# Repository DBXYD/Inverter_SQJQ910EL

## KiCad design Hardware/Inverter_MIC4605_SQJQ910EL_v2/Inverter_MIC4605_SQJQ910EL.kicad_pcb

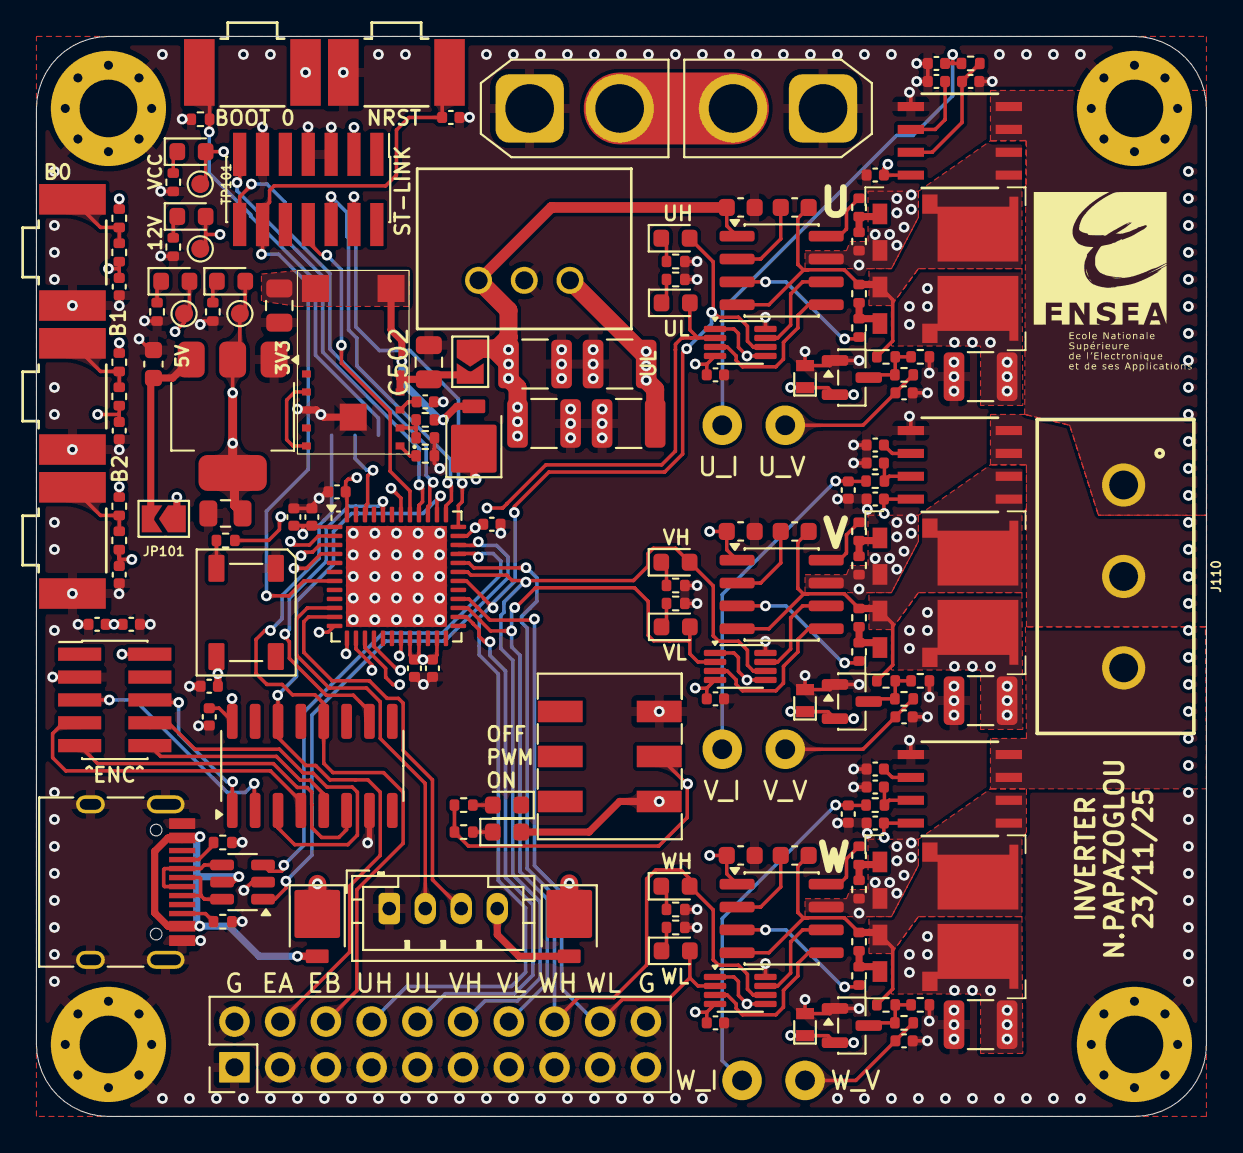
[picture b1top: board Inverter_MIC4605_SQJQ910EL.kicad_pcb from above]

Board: 6 copper layers, 65.0 x 60.0 mm, 170 parts (1 on the bottom side), 108 nets.

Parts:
C101, C102, C103, C104, C105, C119, C139, C140, C142, C207, C209, C307, C309, C407, C409: 100n; C_0402_1005Metric
C106: 4u7; C_0402_1005Metric
C107, C110, C128, C204, C205, C206, C208, C304, C305, C306, C308, C404, C405, C406, C408: 10n; C_0402_1005Metric
C108: 10u; C_0603_1608Metric
C109: 22u; C_0805_2012Metric
C141, C504: 1u; C_0402_1005Metric
C201, C202, C301, C302, C401, C402: 1u; C_0603_1608Metric
C203, C303, C403, C701, C702: 10u; C_1210_3225Metric
C502: 10u; C_0805_2012Metric
C503: 47u; C_0805_2012Metric
C703, C704: 22u; C_1210_3225Metric
D101, D103, D104: SS2P5-M3/84A; D_SMP_DO-220AA
D102: WS2812B; LED_WS2812B_PLCC4_5.0x5.0mm_P3.2mm
D105, D106, D107, D108, D109, D110, D201, D202, D301, D302, D401, D402: LED; LED_0603_1608Metric
D203, D303, D403: 824032813; WE 824032813
D204, D304, D404: BAT54S; SOT-23
H101, H102, H105, H106: MountingHole_Pad; MountingHole_3.2mm_M3_Pad_Via
J101, J102: Conn_01x02; AMASS_XT30U-M_1x02_P5.0mm_Vertical
J104: PinHeader_2x07_P1.27mm_Vertical_SMD
J106: 629722000214; USB_C_Receptacle_HRO_TYPE-C-31-M-12
J107: Conn_02x05_Odd_Even; PinHeader_2x05_P1.27mm_Vertical_SMD
J108: Conn_01x04; JST_PH_B4B-PH-K_1x04_P2.00mm_Vertical
J109: Conn_02x10_Odd_Even; PinHeader_2x10_P2.54mm_Vertical
J110: Conn_01x03; WE 691311500103
JP101, JP501: SolderJumper_2_Open; SolderJumper-2_P1.3mm_Open_TrianglePad1.0x1.5mm
JP102: Jumper_3_Open; SolderJumper-3_P1.3mm_Open_RoundedPad1.0x1.5mm
R101, R102, R103, R104, R106, R107, R112, R202, R205, R209, R210, R302, R305, R309, R310, R402, R405, R409, R410: 10k; R_0402_1005Metric
R105: 330; R_0402_1005Metric
R108: 12k; R_0402_1005Metric
R109: 10k2; R_0402_1005Metric
R110: 3k2; R_0402_1005Metric
R111, R206, R207, R306, R307, R406, R407: 1k5; R_0402_1005Metric
R113, R114: 1k1; R_0402_1005Metric
R115, R116: 5k1; R_0402_1005Metric
R201, R204, R301, R304, R401, R404: 33; R_0402_1005Metric
R203, R303, R403: 1k; R_0402_1005Metric
R208, R308, R408: 180k; R_0402_1005Metric
R501: 402k; R_0402_1005Metric
R502: 80k6; R_0402_1005Metric
R503: 5k6; R_0402_1005Metric
SW101, SW102, SW103, SW104, SW105: SW_Push; KSS221GLFS
SW106: SW_Slide_DPDT; WE 452406020024
TP101, TP102: 24V; TestPoint_Pad_D1.0mm
TP103: 5V; TestPoint_Pad_D1.0mm
TP104: 3V3; TestPoint_Pad_D1.0mm
TP105, TP106, TP107, TP108, TP109, TP110: Pin_D1.1mm_L8.5mm_W2.5mm_FlatFork
U101: AZ1117-3.3; SOT-223
U102: STM32G431CBUx; QFN-48-1EP_7x7mm_P0.5mm_EP5.6x5.6mm
U103: USBLC6-2SC6; SOT-23-6
U104: MAX3097ECSE+; SOIC-16_3.9x9.9mm_P1.27mm
U201, U301, U401: SQJQ910EL
U202, U302, U402: SN74LVC2G08; VSSOP-8_2.3x2mm_P0.5mm
U203, U303, U403: MIC4605-1YM; SOIC-8_3.9x4.9mm_P1.27mm
U204, U304, U404: GO 10-SME/SP3; SOIC8-GO-SME&slash_SP3_LEM
U501: WE 171013801
U701: WE 173951275

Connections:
+3.3V: C101.1, C102.1, C103.2, C104.1, C105.1, C106.1, C109.1, C140.2, C204.1, C207.1, C304.1, C307.1, C404.1, C407.1, D108.2 (A), D109.2 (A), D203.1 (A1), D204.2 (K), D303.1 (A1), D304.2 (K), D403.1 (A1), D404.2 (K), J104.3 (VCC), R101.2, R103.2, R106.2, SW104.1, SW106.1 (A), TP104.1, U101.2 (VO), U101.4 (VO), U102.1 (VBAT), U102.20 (VREF+), U102.21 (VDDA), U102.23 (VDD), U102.35 (VDD), U102.48 (VDD), U104.16 (VCC), U202.4 (GND), U204.8 (UC), U302.4 (GND), U304.8 (UC), U402.4 (GND), U404.8 (UC)
+5V: C119.2, C141.1, C142.2, D101.1 (K), D102.1 (VDD), D103.1 (K), D104.1 (K), D107.2 (A), J107.2, JP101.1 (A), TP103.1
+12V: C201.1, C301.1, C401.1, C703.1, C704.1, D106.2 (A), JP501.1 (A), TP102.1, U203.1 (Vdd), U303.1 (Vdd), U403.1 (Vdd), U701.3 (12V)
/5V_BUCK: C503.1, D101.2 (A), R501.1, U501.6 (VOUT), U501.7 (VOUT)
/5V_UART: D104.2 (A), J108.4
/5V_USB: D103.2 (A), J106.A4 (VBUS), J106.A9 (VBUS), J106.B4 (VBUS), J106.B9 (VBUS), U103.5 (VBUS)
/A: J107.6, U104.1 (A)
/B: J107.8, U104.3 (B)
/BOOT_0: JP102.1 (A), R112.2, SW104.2
/BTN_0: C107.1, R102.1, U102.2 (PC13)
/BTN_1: C110.1, R104.1, U102.3 (PC14)
/BTN_2: C128.1, R107.1, U102.4 (PC15)
/D+: J106.A6 (D+), J106.B6 (D+), U103.6 (I/O1)
/D-: J106.A7 (D-), J106.B7 (D-), U103.4 (I/O2)
/EXT_RX: J108.3, U102.11 (PA3)
/EXT_TX: J108.2, U102.10 (PA2)
/MIC4605_SQJQ910EL_U/BM: C202.2, R202.2, R208.2, U201.3 (S), U201.5 (D), U203.4 (HS), U204.1 (IP+), U204.2 (IP+)
/MIC4605_SQJQ910EL_U/CMD_H: R201.1, U203.3 (HO)
/MIC4605_SQJQ910EL_U/CMD_L: R204.1, U203.8 (LO)
/MIC4605_SQJQ910EL_U/HB: C202.1, U203.2 (HB)
/MIC4605_SQJQ910EL_U/Imes: C205.1, R203.1, U204.7 (UOUT)
/MIC4605_SQJQ910EL_U/Uref: C206.1, U204.6 (UREF)
/MIC4605_SQJQ910EL_V/BM: C302.2, R302.2, R308.2, U301.3 (S), U301.5 (D), U303.4 (HS), U304.1 (IP+), U304.2 (IP+)
/MIC4605_SQJQ910EL_V/CMD_H: R301.1, U303.3 (HO)
/MIC4605_SQJQ910EL_V/CMD_L: R304.1, U303.8 (LO)
/MIC4605_SQJQ910EL_V/HB: C302.1, U303.2 (HB)
/MIC4605_SQJQ910EL_V/Imes: C305.1, R303.1, U304.7 (UOUT)
/MIC4605_SQJQ910EL_V/Uref: C306.1, U304.6 (UREF)
/MIC4605_SQJQ910EL_W/BM: C402.2, R402.2, R408.2, U401.3 (S), U401.5 (D), U403.4 (HS), U404.1 (IP+), U404.2 (IP+)
/MIC4605_SQJQ910EL_W/CMD_H: R401.1, U403.3 (HO)
/MIC4605_SQJQ910EL_W/CMD_L: R404.1, U403.8 (LO)
/MIC4605_SQJQ910EL_W/HB: C402.1, U403.2 (HB)
/MIC4605_SQJQ910EL_W/Imes: C405.1, R403.1, U404.7 (UOUT)
/MIC4605_SQJQ910EL_W/Uref: C406.1, U404.6 (UREF)
/NEO_PWM: R105.1, U102.42 (PB4)
/NRST: C139.1, J104.12 (~RST), SW105.1, U102.7 (PG10)
/OUT_A: J109.4, U102.38 (PA15), U104.14 (OutA)
/OUT_B: J109.6, JP102.3 (B), U104.12 (OutB)
/OUT_Z: U102.44 (PB6), U104.10 (OutZ)
/PWM_EN: R113.2, R114.1, SW106.2 (B), U202.1, U202.5, U302.1, U302.5, U402.1, U402.5
/PWM_U_H: D201.2 (A), J109.8, U102.30 (PA8), U202.6
/PWM_U_L: D202.2 (A), J109.10, U102.26 (PB13), U202.2
/PWM_V_H: D301.2 (A), J109.12, U102.31 (PA9), U302.6
/PWM_V_L: D302.2 (A), J109.14, U102.27 (PB14), U302.2
/PWM_W_H: D401.2 (A), J109.16, U102.32 (PA10), U402.6
/PWM_W_L: D402.2 (A), J109.18, U102.28 (PB15), U402.2
/SWCLK: J104.6 (JCLK/SWCLK), U102.37 (PA14)
/SWDIO: J104.4 (JTMS/SWDIO), U102.36 (PA13)
/SWO: J104.8 (JTDO/SWO), U102.41 (PB3)
/USB_DN: U102.33 (PA11), U103.3 (I/O2)
/USB_DP: U102.34 (PA12), U103.1 (I/O1)
/U_I_Sense: C208.1, R203.2, TP106.1, U102.19 (PB2)
/U_OUT: J110.1, U204.3 (IP-), U204.4 (IP-)
/U_V_Sense: C209.1, R209.2, TP105.1, U102.16 (PC4)
/VCP_RX: J104.13 (VCP_RX), U102.40 (PC11)
/VCP_TX: J104.14 (VCP_TX), U102.39 (PC10)
/V_I_Sense: C308.1, R303.2, TP108.1, U102.15 (PA7)
/V_OUT: J110.2, U304.3 (IP-), U304.4 (IP-)
/V_V_Sense: C309.1, R309.2, TP107.1, U102.14 (PA6)
/W_I_Sense: C408.1, R403.2, TP110.1, U102.12 (PA4)
/W_OUT: J110.3, U404.3 (IP-), U404.4 (IP-)
/W_V_Sense: C409.1, R409.2, TP109.1, U102.13 (PA5)
/Z: J107.10, U104.5 (Z)
//A: J107.5, U104.2 (/A)
//B: J107.7, U104.4 (/B)
//Z: J107.9, U104.6 (/Z)
GND: C101.2, C102.2, C103.1, C104.2, C105.2, C106.2, C107.2, C108.2, C109.2, C110.2, C119.1, C128.2, C139.2, C140.1, C141.2, C142.1, C201.2, C203.2, C204.2, C205.2, C206.2, C207.2, C208.2, C209.2, C301.2, C303.2, C304.2, C305.2, C306.2, C307.2, C308.2, C309.2, C401.2, C403.2, C404.2, C405.2, C406.2, C407.2, C408.2, C409.2, C502.2, C503.2, C504.2, C701.2, C702.2, C703.2, C704.2, D102.3 (VSS), D110.1 (K), D203.2 (A2), D204.1 (A), D303.2 (A2), D304.1 (A), D403.2 (A2), D404.1 (A), H101.1, H102.1, H105.1, H106.1, J101.1, J102.1, J104.5 (GND), J104.7 (GND), J104.11 (GNDDetect), J106.A1 (GND), J106.A12 (GND), J106.B1 (GND), J106.B12 (GND), J106.S1 (SHIELD), J107.3, J108.1, J109.1, J109.2, J109.3, J109.5, J109.7, J109.9, J109.11, J109.13, J109.15, J109.17, J109.19, J109.20, R108.2, R109.2, R110.2, R111.2, R112.1, R115.1, R116.2, R205.2, R206.2, R207.2, R210.2, R305.2, R306.2, R307.2, R310.2, R405.2, R406.2, R407.2, R410.2, R502.2, R503.2, SW101.2, SW102.2, SW103.2, SW105.2, SW106.3 (C), U101.1 (GND), U102.49 (VSS), U103.2 (GND), U104.7 (GND), U201.2 (S), U202.8 (Vcc), U203.7 (Vss), U204.5 (GND), U301.2 (S), U302.8 (Vcc), U303.7 (Vss), U304.5 (GND), U401.2 (S), U402.8 (Vcc), U403.7 (Vss), U404.5 (GND), U501.10 (AGND), U501.13 (PGND), U701.2 (GND)
unnamed: D102.4 (DIN), R105.2
unnamed: D105.1 (K), R108.1
unnamed: D106.1 (K), R109.1
unnamed: D107.1 (K), R110.1
unnamed: D108.1 (K), R111.1
unnamed: D109.1 (K), R113.1
unnamed: D110.2 (A), R114.2
unnamed: D201.1 (K), R206.1
unnamed: D202.1 (K), R207.1
unnamed: D204.3 (common), R208.1, R209.1, R210.1
unnamed: D301.1 (K), R306.1
unnamed: D302.1 (K), R307.1
unnamed: D304.3 (common), R308.1, R309.1, R310.1
unnamed: D401.1 (K), R406.1
unnamed: D402.1 (K), R407.1
unnamed: D404.3 (common), R408.1, R409.1, R410.1
unnamed: J106.A5 (CC1), R115.2
unnamed: J106.B5 (CC2), R116.1
unnamed: C108.1, JP101.2 (B), U101.3 (VI)
unnamed: JP102.2 (C), U102.46 (PB8)
unnamed: R101.1, R102.2, SW101.1
unnamed: R103.1, R104.2, SW102.1
unnamed: R106.1, R107.2, SW103.1
unnamed: R204.2, R205.1, U201.1 (G)
unnamed: R201.2, R202.1, U201.4 (G)
unnamed: U202.3, U203.5 (HI)
unnamed: U202.7, U203.6 (LI)
unnamed: R304.2, R305.1, U301.1 (G)
unnamed: R301.2, R302.1, U301.4 (G)
unnamed: U302.3, U303.5 (HI)
unnamed: U302.7, U303.6 (LI)
unnamed: R404.2, R405.1, U401.1 (G)
unnamed: R401.2, R402.1, U401.4 (G)
unnamed: U402.3, U403.5 (HI)
unnamed: U402.7, U403.6 (LI)
unnamed: U501.9 (VIN_LINK), U501.12 (En)
unnamed: R501.2, R502.1, U501.2 (FB)
unnamed: R503.1, U501.1 (FSW)
unnamed: C504.1, U501.3 (Vcc)
VCC: C203.1, C303.1, C403.1, C701.1, C702.1, D105.2 (A), J101.2, J102.2, TP101.1, U201.6 (D), U301.6 (D), U401.6 (D), U701.1 (VIN)
VIN: C502.1, JP501.2 (B), U501.4 (VIN), U501.5 (VIN)

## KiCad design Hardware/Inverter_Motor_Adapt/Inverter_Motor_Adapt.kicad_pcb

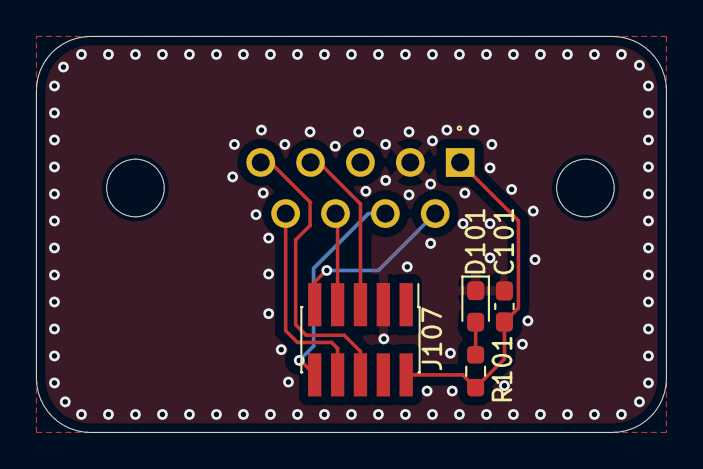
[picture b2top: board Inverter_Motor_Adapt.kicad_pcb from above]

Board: 2 copper layers, 35.0 x 22.0 mm, 5 parts (1 on the bottom side), 9 nets.

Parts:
C101: 100n; C_0603_1608Metric_Pad1.08x0.95mm_HandSolder
D101: LED; LED_0603_1608Metric_Pad1.05x0.95mm_HandSolder
J101: DE9_Pins; DSUB-9_Pins_Vertical_P2.77x2.84mm
J107: Conn_02x05_Odd_Even; PinHeader_2x05_P1.27mm_Vertical_SMD
R101: 3k3; R_0603_1608Metric_Pad0.98x0.95mm_HandSolder

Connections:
+5V: C101.1, J101.1, J107.2, R101.1
/A: J101.5, J107.6
/B: J101.9, J107.8
/Z: J101.7, J107.10
//A: J101.4, J107.5
//B: J101.8, J107.7
//Z: J101.6, J107.9
GND: C101.2, D101.1 (K), J101.2, J107.3
unnamed: D101.2 (A), R101.2

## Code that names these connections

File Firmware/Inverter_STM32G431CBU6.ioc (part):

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Mcu.Name=STM32G431C(6-8-B)Ux
Mcu.Package=UFQFPN48
Mcu.UserName=STM32G431CBUx
PA10.GPIOParameters=GPIO_Label
PA10.GPIO_Label=PWM_W_H
PA10.Signal=S_TIM1_CH3
PA11.Mode=Device
PA11.Signal=USB_DM
PA12.Mode=Device
PA12.Signal=USB_DP
PA13.Mode=Trace_Asynchronous_SW
PA13.Signal=SYS_JTMS-SWDIO
PA14.Mode=Trace_Asynchronous_SW
PA14.Signal=SYS_JTCK-SWCLK
PA15.GPIOParameters=GPIO_Label
PA15.GPIO_Label=ENC_A
PA15.Signal=S_TIM8_CH1
PA2.GPIOParameters=GPIO_Label
PA2.GPIO_Label=EXT_TX
PA2.Mode=Asynchronous
PA2.Signal=USART2_TX
PA3.GPIOParameters=GPIO_Label
PA3.GPIO_Label=EXT_RX
PA3.Mode=Asynchronous
PA3.Signal=USART2_RX
PA4.GPIOParameters=GPIO_Label
PA4.GPIO_Label=W_I_Sense
PA4.Mode=IN17-Single-Ended
PA4.Signal=ADC2_IN17
PA5.GPIOParameters=GPIO_Label
PA5.GPIO_Label=W_V_Sense
PA5.Mode=IN13-Single-Ended
PA5.Signal=ADC2_IN13
PA6.GPIOParameters=GPIO_Label
PA6.GPIO_Label=V_V_Sense
PA6.Mode=IN3-Single-Ended
PA6.Signal=ADC2_IN3
PA7.GPIOParameters=GPIO_Label
PA7.GPIO_Label=V_I_Sense
PA7.Mode=IN4-Single-Ended
PA7.Signal=ADC2_IN4
PA8.GPIOParameters=GPIO_Label
PA8.GPIO_Label=PWM_U_H
PA8.Signal=S_TIM1_CH1
PA9.GPIOParameters=GPIO_Label
PA9.GPIO_Label=PWM_V_H
PA9.Signal=S_TIM1_CH2
PB13.GPIOParameters=GPIO_Label
PB13.GPIO_Label=PWM_U_L
PB13.Mode=PWM Generation1 CH1 CH1N
PB13.Signal=TIM1_CH1N
PB14.GPIOParameters=GPIO_Label
PB14.GPIO_Label=PWM_V_L
PB14.Mode=PWM Generation2 CH2 CH2N
PB14.Signal=TIM1_CH2N
PB15.GPIOParameters=GPIO_Label
PB15.GPIO_Label=PWM_W_L
PB15.Mode=PWM Generation3 CH3 CH3N
PB15.Signal=TIM1_CH3N
PB2.GPIOParameters=GPIO_Label
PB2.GPIO_Label=U_I_Sense
PB2.Mode=IN12-Single-Ended
PB2.Signal=ADC2_IN12
PB3.Mode=Trace_Asynchronous_SW
PB3.Signal=SYS_JTDO-SWO
PB4.GPIOParameters=GPIO_Label
PB4.GPIO_Label=PWM_NEO
PB4.Signal=S_TIM3_CH1
PB6.GPIOParameters=GPIO_Label
PB6.GPIO_Label=ENC_Z
PB6.Signal=S_TIM8_ETR
PB8-BOOT0.GPIOParameters=GPIO_Label
PB8-BOOT0.GPIO_Label=ENC_B
PB8-BOOT0.Signal=S_TIM8_CH2
PC10.GPIOParameters=GPIO_Label
PC10.GPIO_Label=VCP_TX
PC10.Mode=Asynchronous
PC10.Signal=USART3_TX
PC11.GPIOParameters=GPIO_Label
PC11.GPIO_Label=VCP_RX
PC11.Mode=Asynchronous
PC11.Signal=USART3_RX
PC13.GPIOParameters=GPIO_Label
PC13.GPIO_Label=BTN_0
PC13.Signal=GPXTI13
PC14-OSC32_IN.GPIOParameters=GPIO_Label
PC14-OSC32_IN.GPIO_Label=BTN_1
PC14-OSC32_IN.Signal=GPXTI14
PC15-OSC32_OUT.GPIOParameters=GPIO_Label
PC15-OSC32_OUT.GPIO_Label=BTN_2
PC15-OSC32_OUT.Signal=GPXTI15
PC4.GPIOParameters=GPIO_Label
PC4.GPIO_Label=U_V_Sense
PC4.Mode=IN5-Single-Ended
PC4.Signal=ADC2_IN5
RCC.HSE_VALUE=8000000
RCC.SYSCLKFreq_VALUE=160000000
RCC.SYSCLKSource=RCC_SYSCLKSOURCE_PLLCLK
board=custom

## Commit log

2026-02-20 add base hardware and firmware
2026-03-14 update code
2026-03-25 update firmware
2026-03-25 add motor/control/fsm
2026-03-27 code last version
